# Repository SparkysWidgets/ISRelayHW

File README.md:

Welcome To: ISRelay Hardware Repo!!
================================

##### Note: This is for the In Series Relay Hardware Version .13 Branch

ISRelay Hardware Design Files in EAGLE. Not much to say, Is consists of mainly Stock parts and is a PTH version!

Schematic Info
-------------------------
##### Schematic is basic and fairly self explanatory

- Input header/Connector (This is usually from a 5V low power MCU)
- BJT acting as a DC current gain switch(~5mA through the BE junction)
- Relay for circuit Isolation from mains
- Flyback, reverse voltage spike protection diode
- LOAD header for connection in series with the HOT line of the mains wiring to be switch
- Added frame to better capture version and project info and license for both board and schem
- Brought info in frame up to date to new site URL schema

Board Layout Info
-------------------------
##### Form Factor based on minimum footprint that can fit this sized relay, can fit into deep outlet boxes

- Creep-age distance between HOT and LV digital side was increased significantly over v11
- Internal cutout added to help the Isolation ^
- Large enough traces to match Relay load specs
- Added traces for LOAD on both sides of PCB as recommended by Relay MFG
- Lengthened traces to both contact sets as recommended by Relay MFG
- Lower portion of GND plane moved!
- Upper portion of GND plane moved!
- Added a bit of a hook up legend below LV connector
- increased creep-age cutout slightly
- changed silk info to reflect new site URL schema

Errata
-------------------------

##### Just a quick list of current issues
- Silkscreen improvements as always 
- Tweak traces a tad bit

Firmware
-------------------------

- There is no firmware (YEEEEES) Feed the control anywhere from ~3.3v to 5v, 5v(higher current source ~80mA for the RZSchrack, and ~100mA for the TE relay)

Using an Arduino to switch on a lamp (DIY Powerswitch tail has never been better!)
-------------------------

A while ago when I first when on this Garden automation adventure(around 2005-06ish), I came across a problem of needed to switch mains pumps, fans and lights. This was before the PST and Sparkfuns Big boy relay kits existed, so I went about source a great relay and some parts to bring it all together.
Since then my awesome much loved Relay is no longer readily available and the similar replacements while adequate don't work quite as well (not a big deal some of the other features are better!)

Feed it 5v, Gnd and a small current ~5ma 5V control signal and the relay does the rest. The units are designed to switch the HOT portion of mains just like a light switch, and use a relay with a high enough specs to drive inductive loads in the range of about 10amps.

Please see [ISRelay's project page](http://www.sparkyswidgets.com/portfolio-item/relaypcb/) for more information!
<http://www.sparkyswidgets.com/portfolio-item/relaypcb/>

License Info
-------------------------

<br />
<span xmlns:dct="http://purl.org/dc/terms/" property="dct:title">ISRelay</span> by <a xmlns:cc="http://creativecommons.org/ns#" href="www.sparkyswidgets.com" property="cc:attributionName" rel="cc:attributionURL">Ryan Edwards, Sparky's Widgets</a> is licensed under a <a rel="license" href="http://creativecommons.org/licenses/by-sa/3.0/deed.en_US">Creative Commons Attribution-ShareAlike 3.0 Unported License</a>.<br />
Based on a work at <a xmlns:dct="http://purl.org/dc/terms/" href="http://www.sparkyswidgets.com/portfolio-item/relaypcb/" rel="dct:source">http://www.sparkyswidgets.com/portfolio-item/relaypcb/</a>

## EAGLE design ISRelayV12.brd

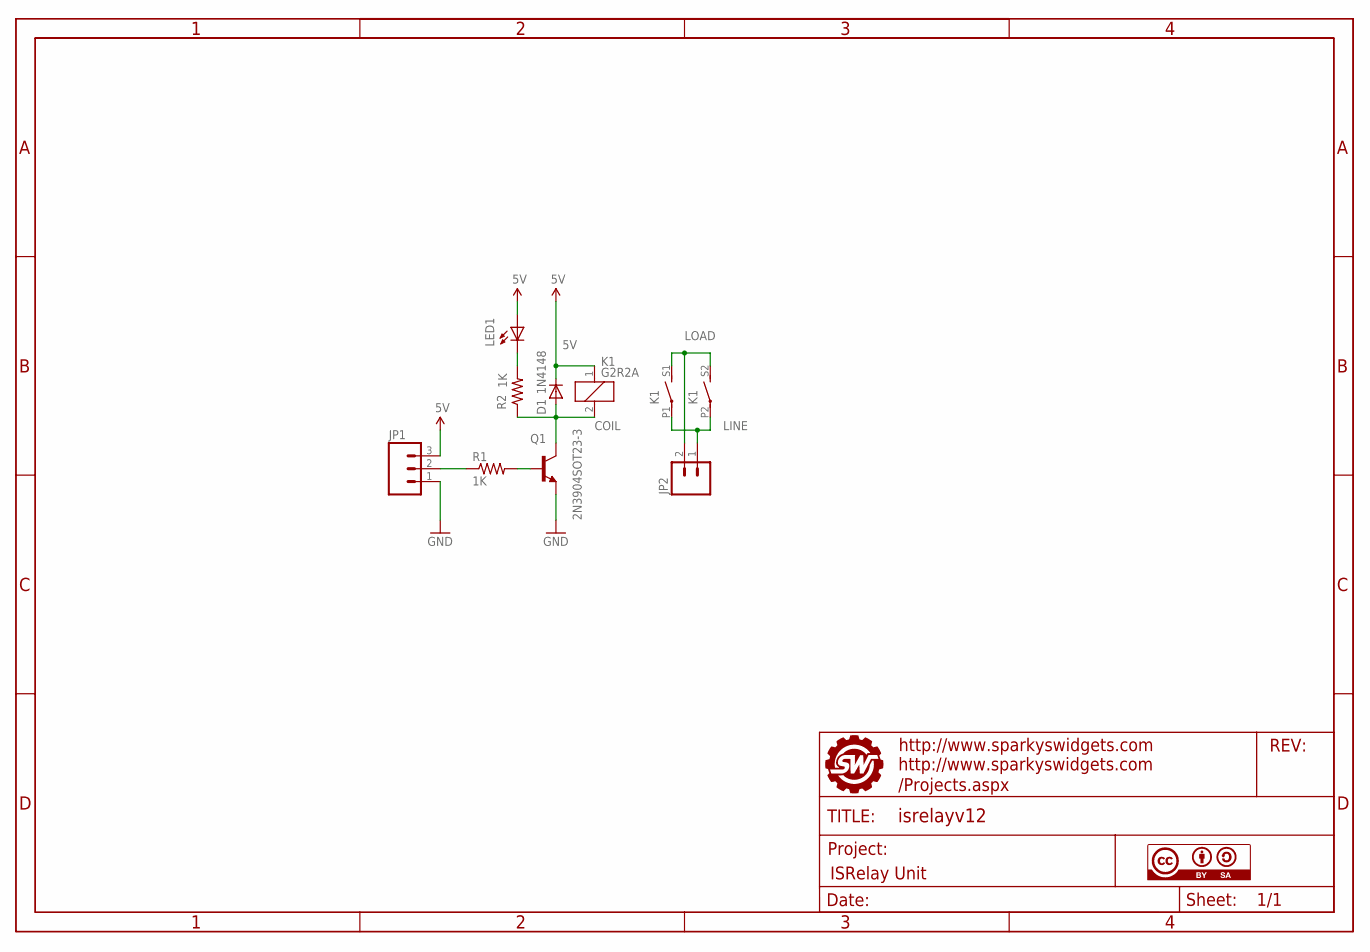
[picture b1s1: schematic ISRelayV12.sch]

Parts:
D1: 1N4148; SOD123
JP1: M03SCREW; SCREWTERMINAL-3.5MM-3
JP2: M025MM; SCREWTERMINAL-5MM-2
K1: G2R2A
LED1: LEDCHIP-LED0805; CHIP-LED0805
Q1: 2N3904SOT23-3; SOT-23
R1, R2: 1K; 0805
U$9: CC-BY-SA
U$11: FRAME_SW_LOGO_CC_BY_SA; SWPCBLOGOWITHINFO

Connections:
5V: D1.C, JP1.3, K1.1, LED1.A
COIL: D1.A, K1.2, Q1.1 (C), R2.1
GND: JP1.1, Q1.2 (E)
LINE: JP2.1, K1.P1, K1.P2
LOAD: JP2.2, K1.S1 (S), K1.S2 (S)
unnamed: Q1.3 (B), R1.2
unnamed: LED1.C, R2.2
RELAY: JP1.2, R1.1

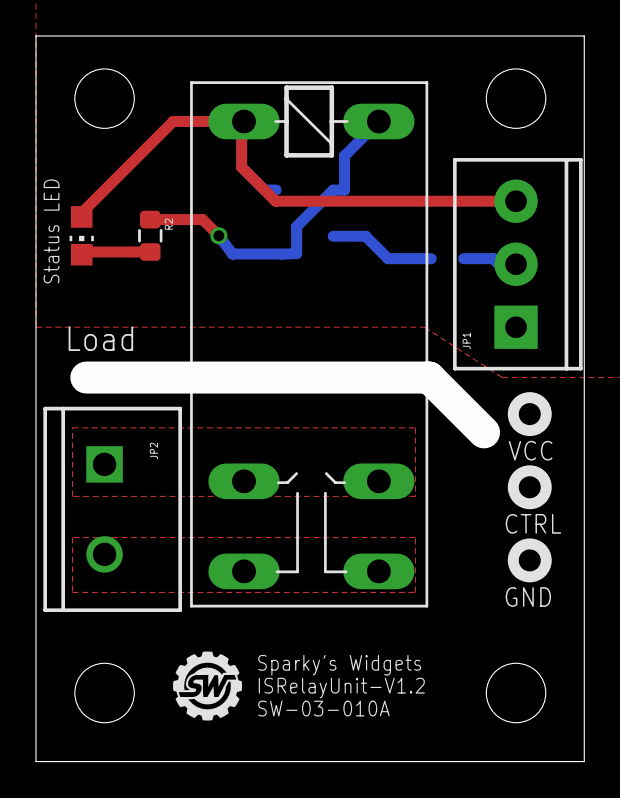
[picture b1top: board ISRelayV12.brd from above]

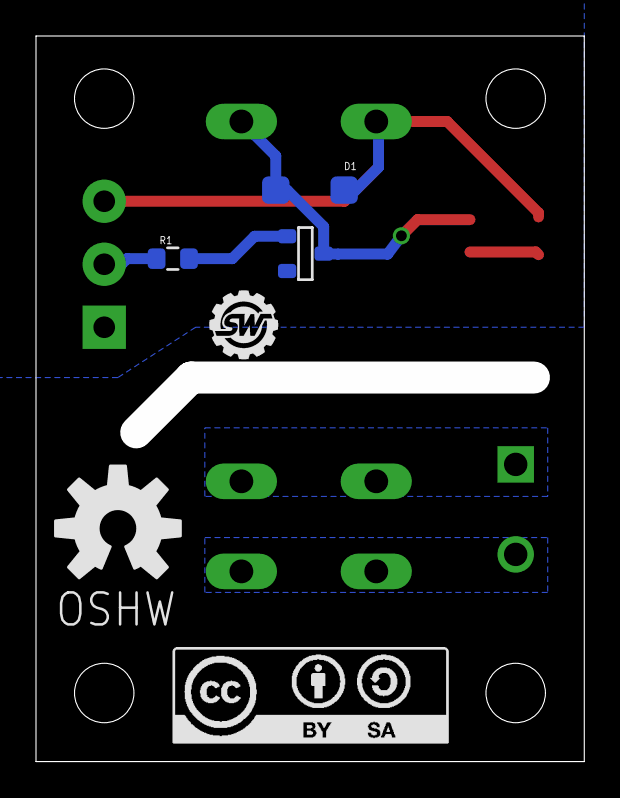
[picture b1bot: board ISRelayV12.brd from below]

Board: 2 copper layers, 28.7 x 38.5 mm, 16 parts (6 on the bottom side), 8 nets.

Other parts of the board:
U$4, U$5, U$6, U$7: STAND-OFF
U$8: SWPCBLOGO
U$10: OSHW-LOGO-L

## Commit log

2013-08-05 First revision of ISRelay finally pushed up
2013-08-05 Fixed readme a bit
2013-08-05 just pushing up file v for old branch
2013-08-05 Added older V11 design for archival
2013-08-06 whatever I messed up a merge lol
2013-08-06 damn you readme, i'll make you love me
2013-08-06 Added the intial SMD version for archival
2013-08-06 Added branch for latest version finally
